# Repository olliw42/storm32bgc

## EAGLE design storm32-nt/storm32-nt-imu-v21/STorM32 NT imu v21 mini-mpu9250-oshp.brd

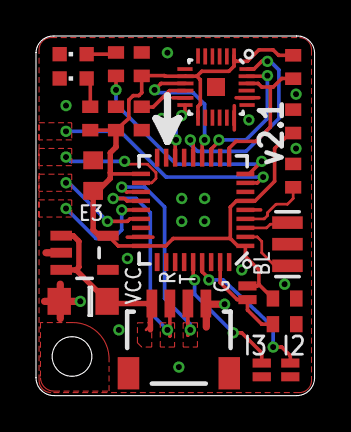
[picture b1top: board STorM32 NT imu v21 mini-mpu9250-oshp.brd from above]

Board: 2 copper layers, 15.5 x 20.0 mm, 22 parts (0 on the bottom side), 20 nets.

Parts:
C1: 10u/6.3V; C0805
C2: 1u; C0603
C3, C4, C5, C6, C8: 100n; C0402
C7: 10n; C0402
IC1: STM32F10XTXU6; VFQFPN36
IC2: SOT23-5
IC3: MPU9250; QFN-24-3X3
LED1: red; CHIPLED_0603
LED2: green; CHIPLED_0603
NT: NT; SM04B-SRSS-TB
Q1: RESONATORSMD; RESONATOR-SMD
R1, R5: 10k; R0402
R2: 4.7k; R0402
R3: 2.2k; R0402
SJ1: BOOT0; SJ_2S-NO
SJ2: IMU-ID2; SJ_2S-NO
SJ3: IMU-ID3; SJ_2S-NO

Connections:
3.3V: C2.1, C4.1, C5.1, C6.1, C7.1, IC1.1, IC1.6, IC1.19, IC1.27, IC2.5, IC3.1, IC3.8, IC3.13, R2.1, R5.2, SJ1.1
5V: C1.1, IC2.1, IC2.3, NT.1
CS: IC1.10, IC3.22, R5.1
GND: C1.2, C2.2, C3.2, C4.2, C5.2, C6.2, C7.2, C8.2, IC1.5, IC1.17, IC1.18, IC1.26, IC1.30, IC1.31, IC1.36, IC2.2, IC3.11, IC3.18, IC3.20, LED1.C, LED2.C, NT.4, Q1.2, R1.1, SJ2.1, SJ3.1
INT: IC1.16, IC3.12
LED: IC1.9, R3.1
unnamed: C3.1, IC1.4
unnamed: LED2.A, R3.2
unnamed: IC1.35, R1.2, SJ1.2
unnamed: IC1.32, SJ3.2
unnamed: IC1.2, Q1.1
unnamed: IC1.3, Q1.3
unnamed: IC1.33, SJ2.2
unnamed: LED1.A, R2.2
unnamed: C8.1, IC3.10
RX: IC1.22, NT.2
SCK: IC1.12, IC3.23
SDI: IC1.14, IC3.24
SDO: IC1.13, IC3.9
TX: IC1.21, NT.3

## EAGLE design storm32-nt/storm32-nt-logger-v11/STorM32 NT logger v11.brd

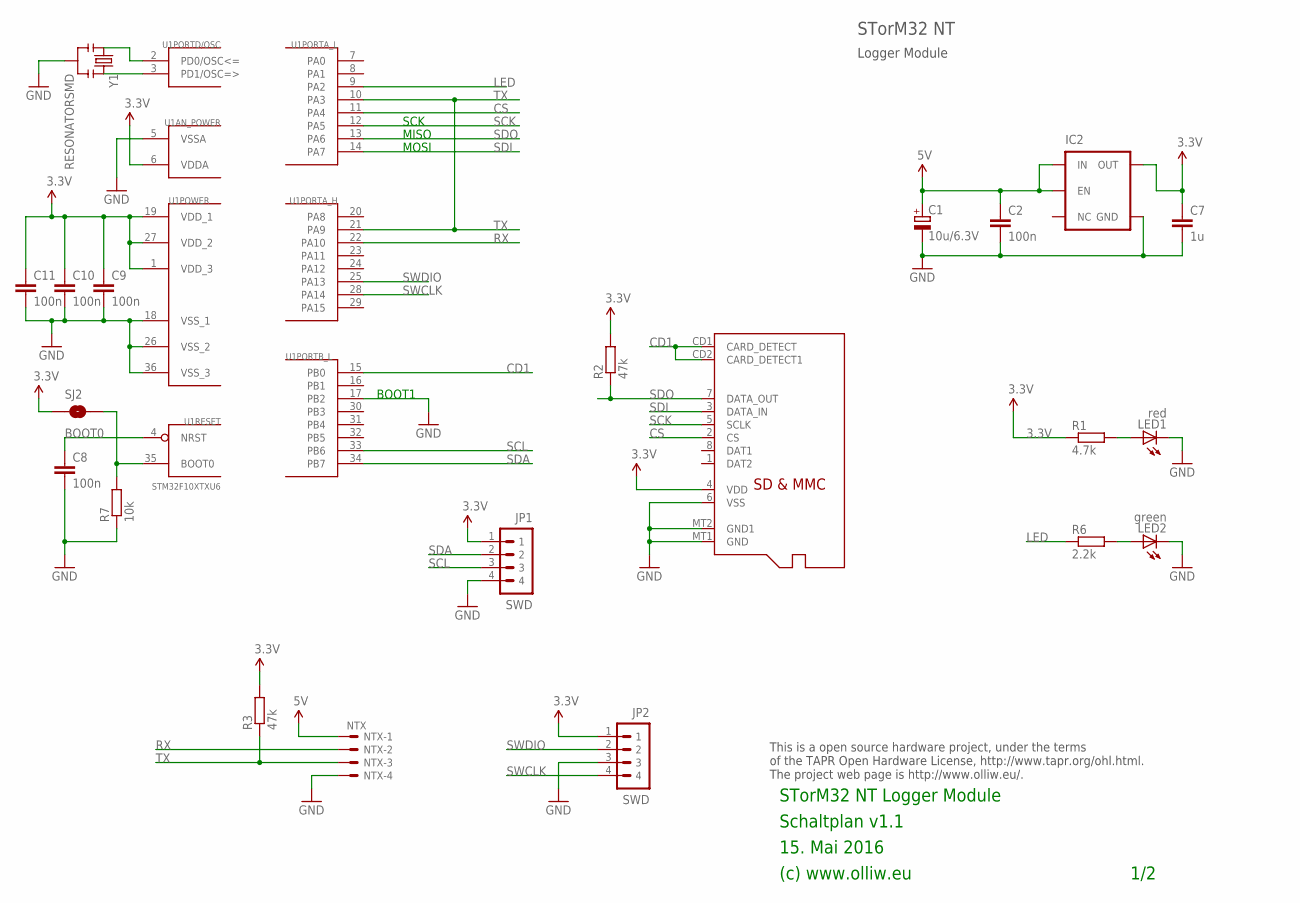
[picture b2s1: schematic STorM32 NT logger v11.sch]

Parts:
C1: 10u/6.3V; SMC_B
C2, C8, C9, C10, C11: 100n; C0603
C7: 1u; C0603
IC2: V_REG_TPS76433SOT23-5; SOT23-5
JP1, JP2: SWD; 4X1_1P27_OCT_BILEX
LED1: red; CHIPLED_0603
LED2: green; CHIPLED_0603
NTX: NTX; SM04B-SRSS-TB
R1: 4.7k; R0603
R2, R3: 47k; R0603
R6: 2.2k; R0603
R7: 10k; R0603
SJ2: BOOT0; SJ_2S-NO
U1: STM32F10XTXU6; VFQFPN36
U$1: MICROSD
Y1: RESONATORSMD; RESONATOR-SMD

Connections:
3.3V: C7.1, C9.1, C10.1, C11.1, IC2.5 (OUT), JP1.1, JP2.1, R1.1, R2.2, R3.2, SJ2.1, U1.1 (VDD_3), U1.6 (VDDA), U1.19 (VDD_1), U1.27 (VDD_2), U$1.4 (VDD)
5V: C1.+, C2.1, IC2.1 (IN), IC2.3 (EN), NTX.1
CD1: U1.15 (PB0), U$1.CD1 (CARD_DETECT), U$1.CD2 (CARD_DETECT1)
CS: U1.11 (PA4), U$1.2 (CS)
GND: C1.-, C2.2, C7.2, C8.2, C9.2, C10.2, C11.2, IC2.2 (GND), JP1.4, JP2.3, LED1.C, LED2.C, NTX.4, R7.1, U1.5 (VSSA), U1.17 (PB2), U1.18 (VSS_1), U1.26 (VSS_2), U1.36 (VSS_3), U$1.6 (VSS), U$1.MT1 (GND), U$1.MT2 (GND1), Y1.2
LED: R6.1, U1.9 (PA2)
unnamed: C8.1, U1.4 (NRST)
unnamed: LED2.A, R6.2
unnamed: R7.2, SJ2.2, U1.35 (BOOT0)
unnamed: U1.2 (PD0/OSC<=), Y1.1
unnamed: U1.3 (PD1/OSC=>), Y1.3
unnamed: LED1.A, R1.2
RX: NTX.2, U1.22 (PA10)
SCK: U1.12 (PA5), U$1.5 (SCLK)
SCL: JP1.3, U1.33 (PB6)
SDA: JP1.2, U1.34 (PB7)
SDI: U1.14 (PA7), U$1.3 (DATA_IN)
SDO: R2.1, U1.13 (PA6), U$1.7 (DATA_OUT)
SWCLK: JP2.4, U1.28 (PA14)
SWDIO: JP2.2, U1.25 (PA13)
TX: NTX.3, R3.1, U1.10 (PA3), U1.21 (PA9)

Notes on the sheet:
15. Mai 2016
(c) www.olliw.eu
STorM32 NT Logger Module
Schaltplan v1.1
This is a open source hardware project, under the terms of the TAPR Open Hardware License, http://www.tapr.org/ohl.html. The project web page is http://www.olliw.eu/.
1/2
Logger Module
STorM32 NT
SCK
MISO
MOSI
BOOT1

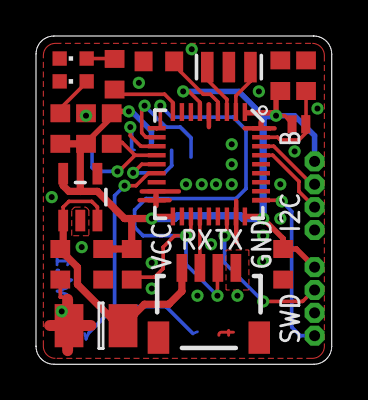
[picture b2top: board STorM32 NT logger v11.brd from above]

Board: 2 copper layers, 16.4 x 18.2 mm, 22 parts (1 on the bottom side), 21 nets.

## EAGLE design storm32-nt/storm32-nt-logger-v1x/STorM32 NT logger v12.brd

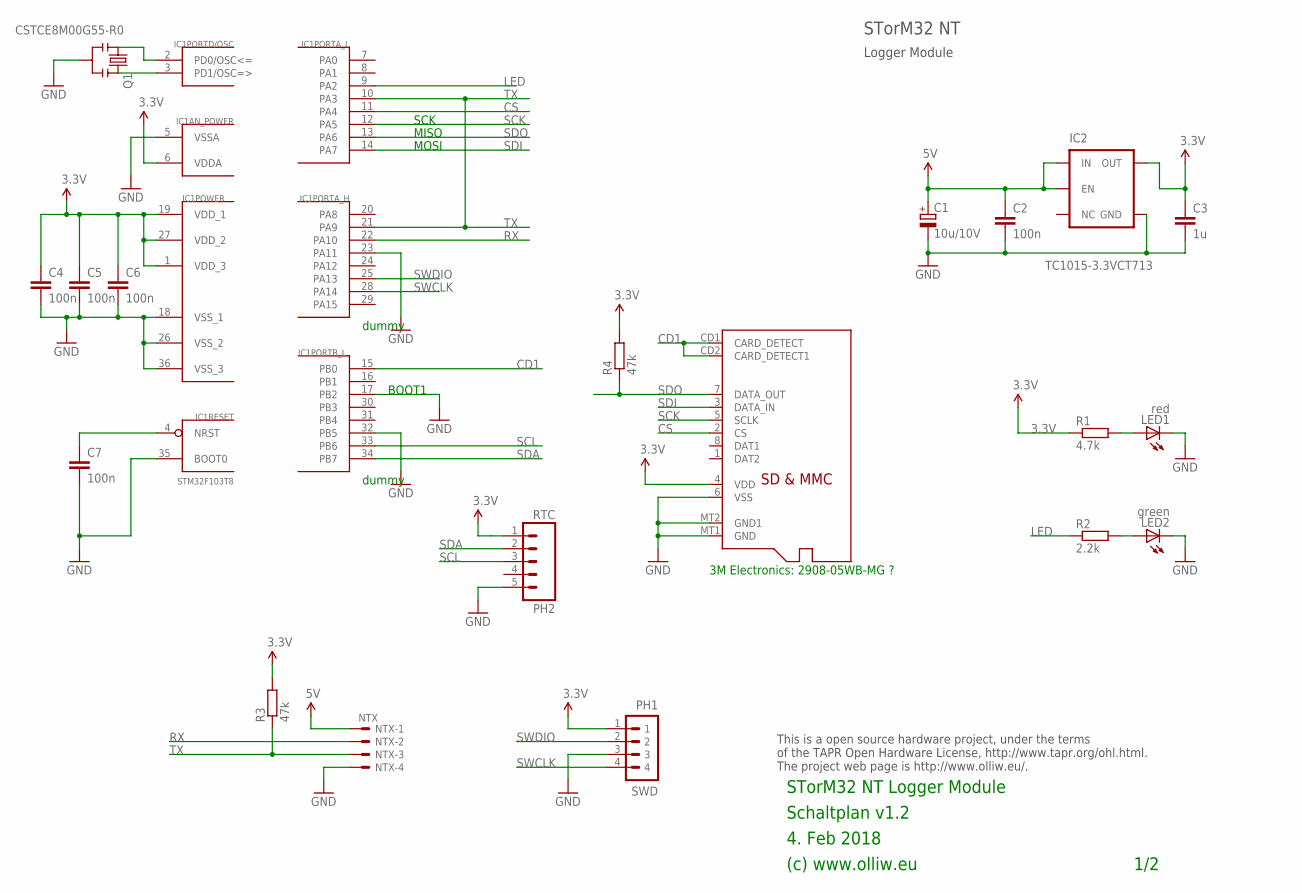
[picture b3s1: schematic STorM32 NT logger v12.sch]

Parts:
C1: 10u/10V; SMC_B
C2, C4, C5, C6, C7: 100n; C0603
C3: 1u; C0603
IC1: STM32F103T8; VFQFPN36
IC2: TC1015-3.3VCT713; SOT23-5
LED1: red; CHIPLED_0603
LED2: green; CHIPLED_0603
NTX: NTX; SM04B-SRSS-TB
PH1: SWD; 4X1_1P27_OCT_BILEX
PH2: RTC; 1X05
Q1: CSTCE8M00G55-R0; RESONATOR-SMD
R1: 4.7k; R0603
R2: 2.2k; R0603
R3, R4: 47k; R0603
U1: 3M 2908-05WB-MG ??; MICROSD

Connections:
3.3V: C3.1, C4.1, C5.1, C6.1, IC1.1 (VDD_3), IC1.6 (VDDA), IC1.19 (VDD_1), IC1.27 (VDD_2), IC2.5 (OUT), PH1.1, PH2.1, R1.1, R3.2, R4.2, U1.4 (VDD)
5V: C1.+, C2.1, IC2.1 (IN), IC2.3 (EN), NTX.1
CD1: IC1.15 (PB0), U1.CD1 (CARD_DETECT), U1.CD2 (CARD_DETECT1)
CS: IC1.11 (PA4), U1.2 (CS)
GND: C1.-, C2.2, C3.2, C4.2, C5.2, C6.2, C7.2, IC1.5 (VSSA), IC1.17 (PB2), IC1.18 (VSS_1), IC1.23 (PA11), IC1.26 (VSS_2), IC1.32 (PB5), IC1.35 (BOOT0), IC1.36 (VSS_3), IC2.2 (GND), LED1.C, LED2.C, NTX.4, PH1.3, PH2.5, Q1.2, U1.6 (VSS), U1.MT1 (GND), U1.MT2 (GND1)
LED: IC1.9 (PA2), R2.1
unnamed: C7.1, IC1.4 (NRST)
unnamed: LED2.A, R2.2
unnamed: IC1.2 (PD0/OSC<=), Q1.1
unnamed: IC1.3 (PD1/OSC=>), Q1.3
unnamed: LED1.A, R1.2
RX: IC1.22 (PA10), NTX.2
SCK: IC1.12 (PA5), U1.5 (SCLK)
SCL: IC1.33 (PB6), PH2.3
SDA: IC1.34 (PB7), PH2.2
SDI: IC1.14 (PA7), U1.3 (DATA_IN)
SDO: IC1.13 (PA6), R4.1, U1.7 (DATA_OUT)
SWCLK: IC1.28 (PA14), PH1.4
SWDIO: IC1.25 (PA13), PH1.2
TX: IC1.10 (PA3), IC1.21 (PA9), NTX.3, R3.1

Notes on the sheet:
4. Feb 2018
(c) www.olliw.eu
STorM32 NT Logger Module
Schaltplan v1.2
This is a open source hardware project, under the terms of the TAPR Open Hardware License, http://www.tapr.org/ohl.html. The project web page is http://www.olliw.eu/.
1/2
Logger Module
STorM32 NT
SCK
MISO
MOSI
BOOT1
dummy
3M Electronics: 2908-05WB-MG ?

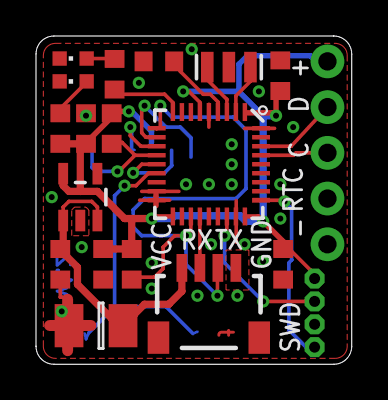
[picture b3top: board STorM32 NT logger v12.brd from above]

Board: 2 copper layers, 17.5 x 18.2 mm, 20 parts (1 on the bottom side), 20 nets.

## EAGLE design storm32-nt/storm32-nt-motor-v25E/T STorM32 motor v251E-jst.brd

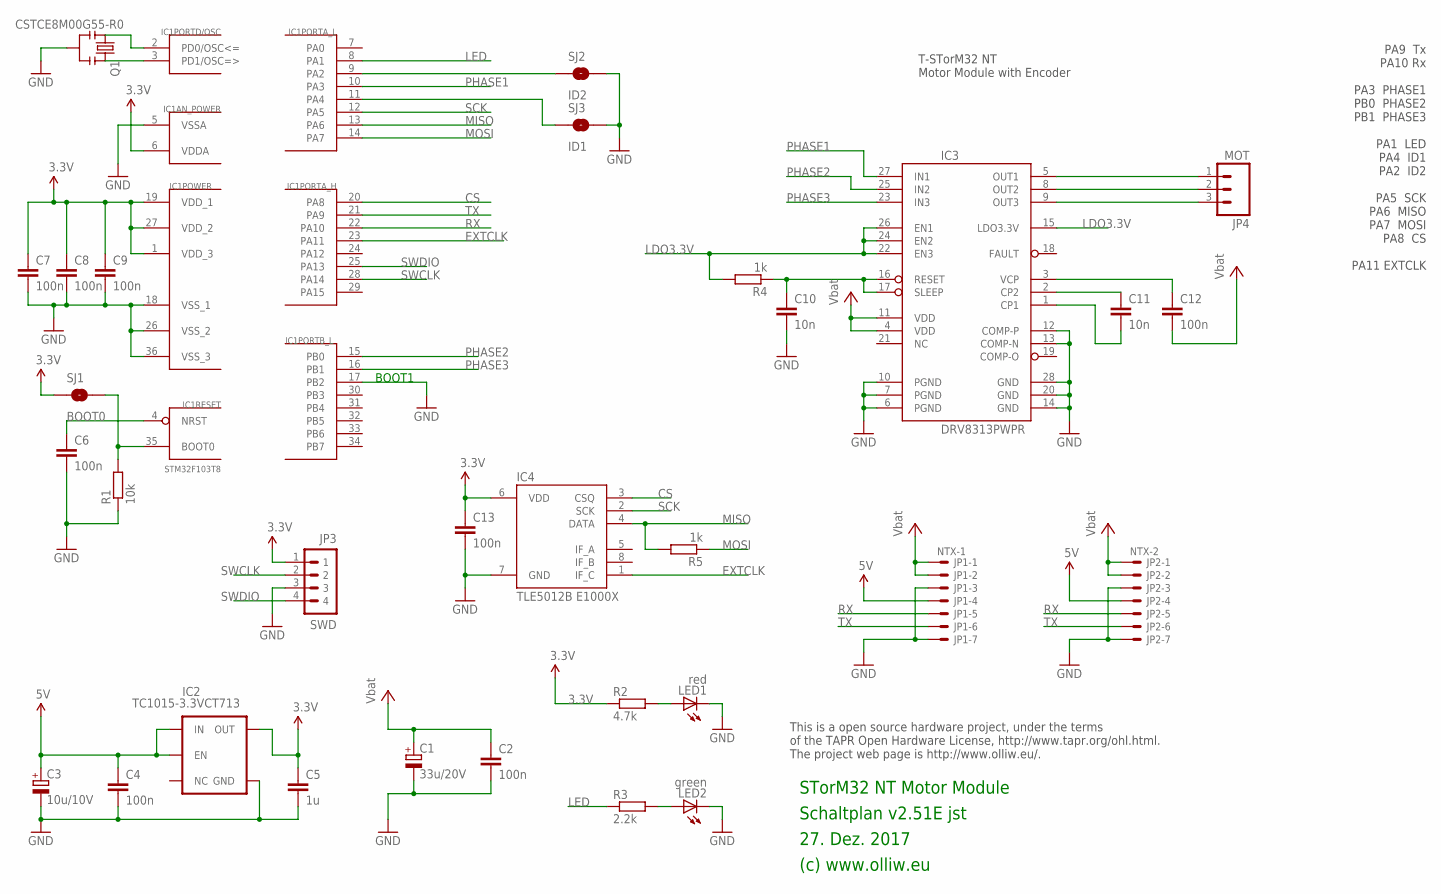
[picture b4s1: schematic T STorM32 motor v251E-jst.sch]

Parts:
C1: 33u/20V; SMC_C
C2, C4, C6, C7, C8, C9, C12, C13: 100n; C0603
C3: 10u/10V; SMC_B
C5: 1u; C0603
C10, C11: 10n; C0603
IC1: STM32F103T8; VFQFPN36
IC2: TC1015-3.3VCT713; SOT23-5
IC3: DRV8313PWPR; HTSSOP28
IC4: TLE5012B E1000X; SO08
JP1: NTX-1; SM07B-SRSS-TB
JP2: NTX-2; SM07B-SRSS-TB
JP3: SWD; 4X1_1P27_OCT_BILEX
JP4: MOT; 1X03
LED1: red; CHIPLED_0603
LED2: green; CHIPLED_0603
Q1: CSTCE8M00G55-R0; RESONATOR-SMD
R1: 10k; R0603
R2: 4.7k; R0603
R3: 2.2k; R0603
R4, R5: 1k; R0603
SJ1: BOOT0; SJ_2S-NO
SJ2: ID2; SJ_2S-NO
SJ3: ID1; SJ_2S-NO

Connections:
3.3V: C5.1, C7.1, C8.1, C9.1, C13.1, IC1.1 (VDD_3), IC1.6 (VDDA), IC1.19 (VDD_1), IC1.27 (VDD_2), IC2.5 (OUT), IC4.6 (VDD), JP3.1, R2.1, SJ1.1
5V: C3.+, C4.1, IC2.1 (IN), IC2.3 (EN), JP1.4, JP2.4
CS: IC1.20 (PA8), IC4.3 (CSQ)
EXTCLK: IC1.23 (PA11), IC4.1 (IF_C)
GND: C1.-, C2.2, C3.-, C4.2, C5.2, C6.2, C7.2, C8.2, C9.2, C10.2, C13.2, IC1.5 (VSSA), IC1.17 (PB2), IC1.18 (VSS_1), IC1.26 (VSS_2), IC1.36 (VSS_3), IC2.2 (GND), IC3.6 (PGND), IC3.7 (PGND), IC3.10 (PGND), IC3.12 (COMP-P), IC3.13 (COMP-N), IC3.14 (GND), IC3.20 (GND), IC3.28 (GND), IC4.7 (GND), JP1.3, JP1.7, JP2.3, JP2.7, JP3.3, LED1.C, LED2.C, Q1.2, R1.1, SJ2.2, SJ3.2
LDO3.3V: IC3.15 (LDO3.3V), IC3.22 (EN3), IC3.24 (EN2), IC3.26 (EN1), R4.2
LED: IC1.8 (PA1), R3.1
MISO: IC1.13 (PA6), IC4.4 (DATA), R5.2
MOSI: IC1.14 (PA7), R5.1
unnamed: IC3.9 (OUT3), JP4.3
unnamed: IC1.9 (PA2), SJ2.1
unnamed: IC1.11 (PA4), SJ3.1
unnamed: C6.1, IC1.4 (NRST)
unnamed: IC1.35 (BOOT0), R1.2, SJ1.2
unnamed: IC1.2 (PD0/OSC<=), Q1.1
unnamed: IC1.3 (PD1/OSC=>), Q1.3
unnamed: LED1.A, R2.2
unnamed: LED2.A, R3.2
unnamed: IC3.8 (OUT2), JP4.2
unnamed: IC3.5 (OUT1), JP4.1
unnamed: C11.1, IC3.2 (CP2)
unnamed: C11.2, IC3.1 (CP1)
unnamed: C10.1, IC3.16 (RESET), IC3.17 (SLEEP), R4.1
unnamed: C12.1, IC3.3 (VCP)
PHASE1: IC1.10 (PA3), IC3.27 (IN1)
PHASE2: IC1.15 (PB0), IC3.25 (IN2)
PHASE3: IC1.16 (PB1), IC3.23 (IN3)
RX: IC1.22 (PA10), JP1.5, JP2.5
SCK: IC1.12 (PA5), IC4.2 (SCK)
SWCLK: IC1.28 (PA14), JP3.2
SWDIO: IC1.25 (PA13), JP3.4
TX: IC1.21 (PA9), JP1.6, JP2.6
VCC: C1.+, C2.1, C12.2, IC3.4 (VDD), IC3.11 (VDD), JP1.1, JP1.2, JP2.1, JP2.2

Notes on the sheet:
27. Dez. 2017
(c) www.olliw.eu
STorM32 NT Motor Module
Schaltplan v2.51E jst
This is a open source hardware project, under the terms of the TAPR Open Hardware License, http://www.tapr.org/ohl.html. The project web page is http://www.olliw.eu/.
T-STorM32 NT Motor Module with Encoder
BOOT1
PA9 Tx PA10 Rx PA3 PHASE1 PB0 PHASE2 PB1 PHASE3 PA1 LED PA4 ID1 PA2 ID2 PA5 SCK PA6 MISO PA7 MOSI PA8 CS PA11 EXTCLK

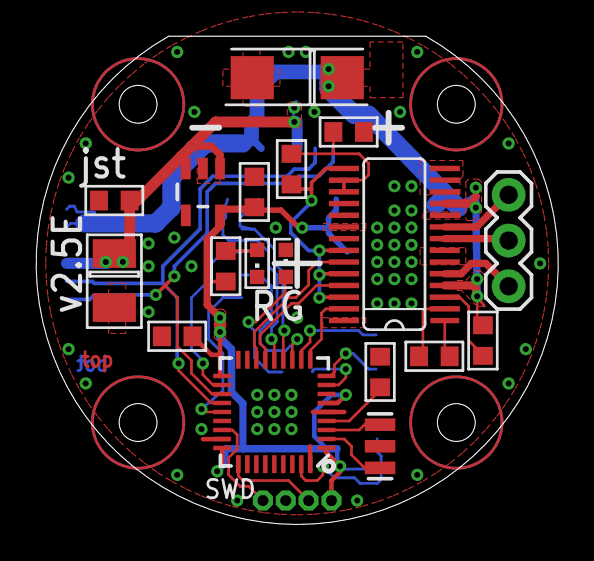
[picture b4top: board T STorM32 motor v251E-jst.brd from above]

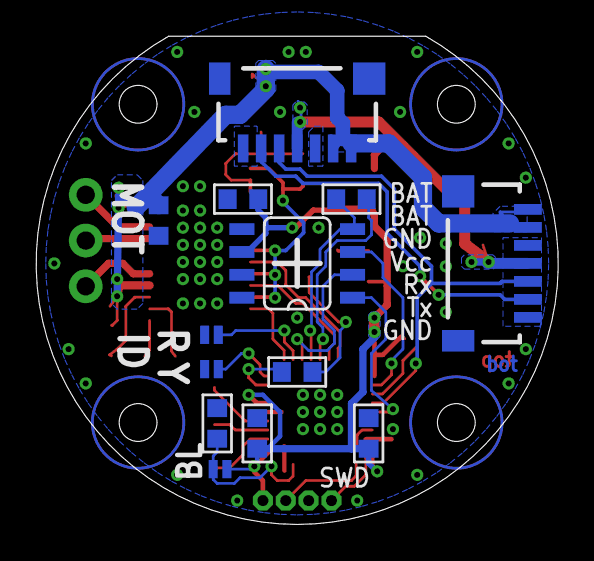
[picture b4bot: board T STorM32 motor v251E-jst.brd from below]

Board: 2 copper layers, 29.0 x 27.1 mm, 32 parts (13 on the bottom side), 33 nets.

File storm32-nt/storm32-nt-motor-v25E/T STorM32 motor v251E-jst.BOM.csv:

"Part";"Value";"Device";"Package";"Description";"";
"C1";"33u/20V";"CPOL-EUSMCC";"SMC_C";"POLARIZED CAPACITOR, European symbol";"";
"C2";"100n";"C-EUC0603";"C0603";"CAPACITOR, European symbol";"";
"C3";"10u/10V";"CPOL-EUSMCB";"SMC_B";"POLARIZED CAPACITOR, European symbol";"";
"C4";"100n";"C-EUC0603";"C0603";"CAPACITOR, European symbol";"";
"C5";"1u";"C-EUC0603";"C0603";"CAPACITOR, European symbol";"";
"C6";"100n";"C-EUC0603";"C0603";"CAPACITOR, European symbol";"";
"C7";"100n";"C-EUC0603";"C0603";"CAPACITOR, European symbol";"";
"C8";"100n";"C-EUC0603";"C0603";"CAPACITOR, European symbol";"";
"C9";"100n";"C-EUC0603";"C0603";"CAPACITOR, European symbol";"";
"C10";"10n";"C-EUC0603";"C0603";"CAPACITOR, European symbol";"";
"C11";"10n";"C-EUC0603";"C0603";"CAPACITOR, European symbol";"";
"C12";"100n";"C-EUC0603";"C0603";"CAPACITOR, European symbol";"";
"C13";"100n";"C-EUC0603";"C0603";"CAPACITOR, European symbol";"";
"IC1";"STM32F103T8";"STM32F10XTXU6";"VFQFPN36";"STM32F101/103 36pad VFQPFN36";"";
"IC2";"TC1015-3.3VCT713";"V_REG_TPS76433SOT23-5";"SOT23-5";"Voltage Regulator";"";
"IC3";"DRV8313PWPR";"DRV8313";"HTSSOP28";"";"";
"IC4";"TLE5012B E1000X";"TLE5012B";"SO08";"";"";
"JP1";"NTX-1";"SM07B-SRSS-TB";"SM07B-SRSS-TB";"Disconnectable Crimp style connector, 1.0mm pitch7 contacts";"";
"JP2";"NTX-2";"SM07B-SRSS-TB";"SM07B-SRSS-TB";"Disconnectable Crimp style connector, 1.0mm pitch7 contacts";"";
"JP3";"SWD";"P4X1_1P27-OCT_BILEX";"4X1_1P27_OCT_BILEX";"";"";
"JP4";"MOT";"M03PTH";"1X03";"Header 3";"";
"LED1";"red";"LEDCHIPLED_0603";"CHIPLED_0603";"LED";"";
"LED2";"green";"LEDCHIPLED_0603";"CHIPLED_0603";"LED";"";
"Q1";"CSTCE8M00G55-R0";"RESONATORSMD";"RESONATOR-SMD";"Resonator";"";
"R1";"10k";"R-EU_R0603";"R0603";"RESISTOR, European symbol";"";
"R2";"4.7k";"R-EU_R0603";"R0603";"RESISTOR, European symbol";"";
"R3";"2.2k";"R-EU_R0603";"R0603";"RESISTOR, European symbol";"";
"R4";"1k";"R-EU_R0603";"R0603";"RESISTOR, European symbol";"";
"R5";"1k";"R-EU_R0603";"R0603";"RESISTOR, European symbol";"";
"SJ1";"BOOT0";"SOLDERJUMPERNO";"SJ_2S-NO";"Solder Jumper";"";
"SJ2";"ID2";"SOLDERJUMPERNO";"SJ_2S-NO";"Solder Jumper";"";
"SJ3";"ID1";"SOLDERJUMPERNO";"SJ_2S-NO";"Solder Jumper";"";

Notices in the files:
parts and their libraries:
Licensing: CC v3.0 Share-Alike You are welcome to use this library for commercial purposes.
